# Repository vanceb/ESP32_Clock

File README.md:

# ESP32_Clock
Clock based on the ESP32

A follow-on from the NightClock

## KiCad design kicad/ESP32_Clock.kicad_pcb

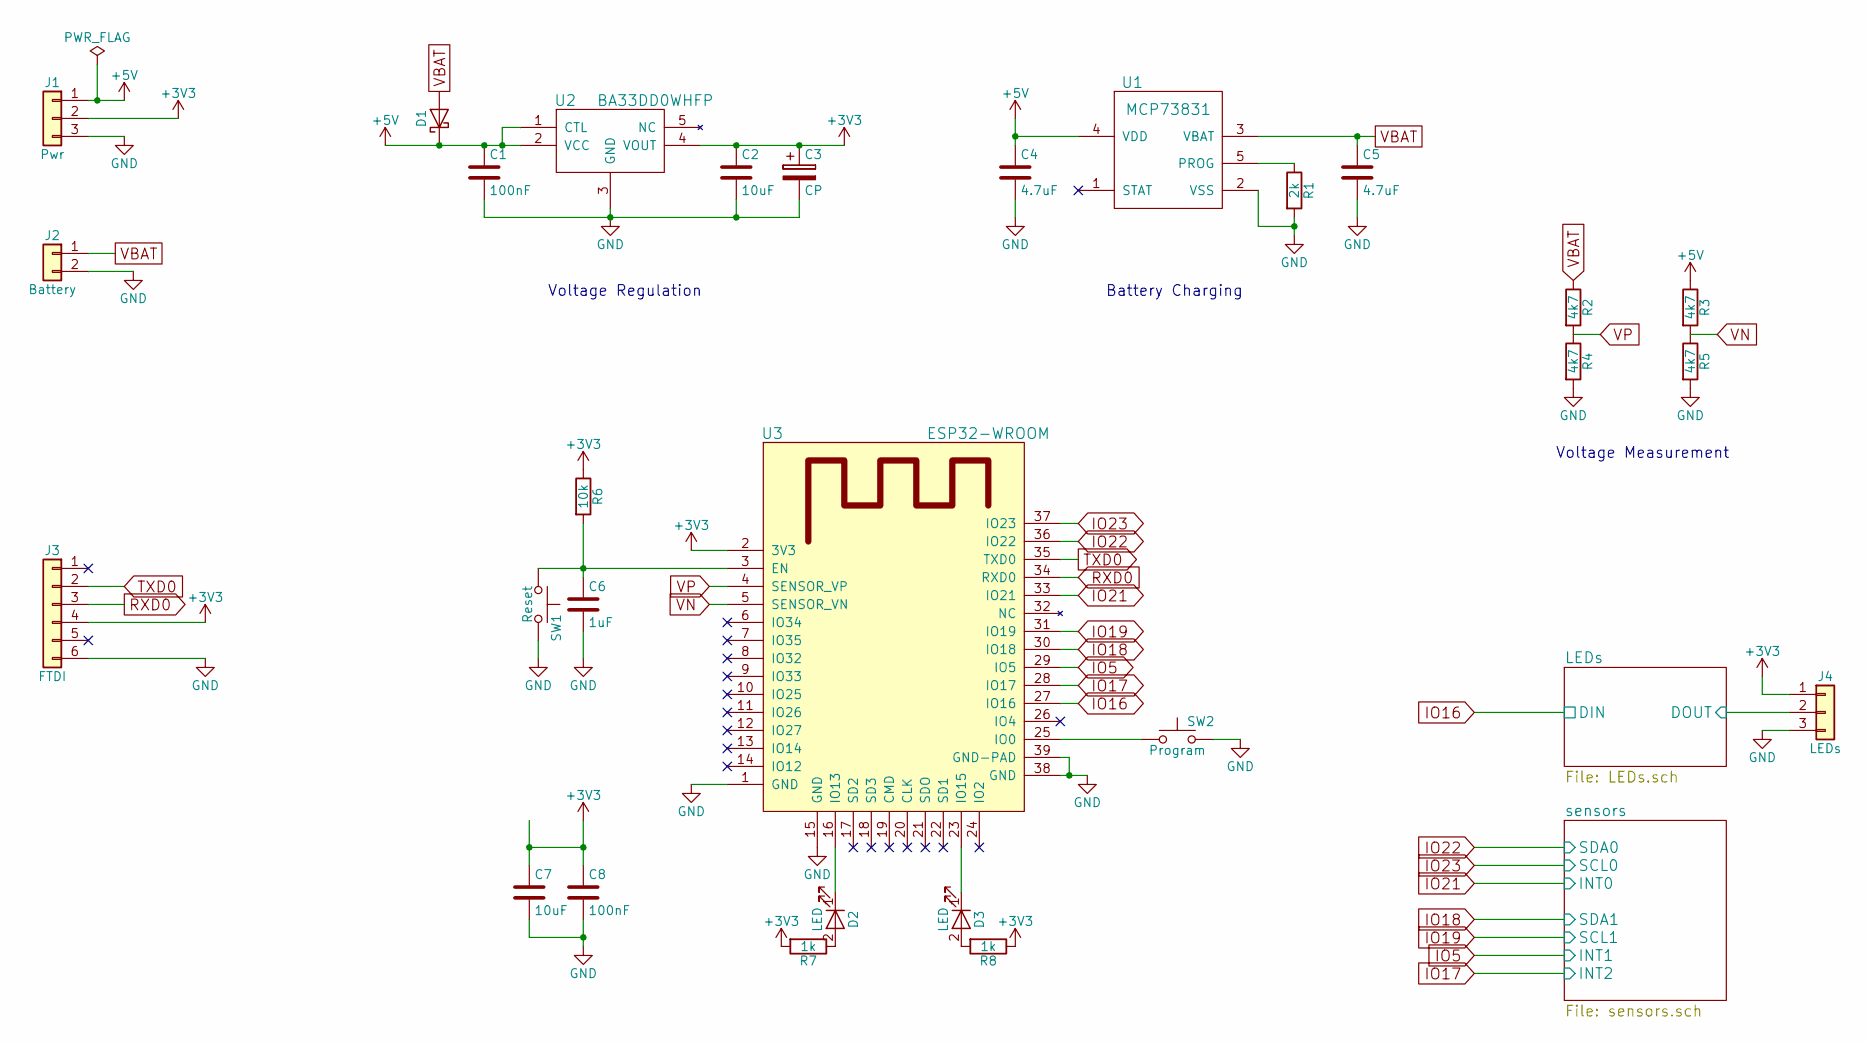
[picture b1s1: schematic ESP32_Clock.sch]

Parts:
C1, C8: 100nF; C_0603_HandSoldering
C2, C7: 10uF; C_0805_HandSoldering
C3: CP; CP_Radial_D8.0mm_P3.50mm
C4, C5: 4.7uF; C_0805_HandSoldering
C6: 1uF; C_0805_HandSoldering
D1: D_SMA_Handsoldering
D2, D3: LED; LED_0603_HandSoldering
J1: Pwr; Pin_Header_Straight_1x03_Pitch2.54mm
J2: Battery; JST_PH_S2B-PH-K_02x2.00mm_Angled
J3: FTDI; Pin_Header_Straight_1x06_Pitch2.54mm
J4: LEDs; Pin_Header_Straight_1x03_Pitch2.54mm
R1: 2k; R_0603_HandSoldering
R2, R3, R4, R5: 4k7; R_0603_HandSoldering
R6: 10k; R_0603_HandSoldering
R7, R8: 1k; R_0603_HandSoldering
SW1: Reset; SW_SPST_EVPBF
SW2: Program; SW_SPST_EVPBF
U1: MCP73831; SOT-23-5_HandSoldering
U2: BA33DD0WHFP; LDO
U3: ESP32-WROOM

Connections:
+3V3: C2.1, C3.1, C7.1, C8.1, J1.2, J3.4, J4.1, R6.1, R7.2, R8.1, U2.4 (VOUT), U3.2 (3V3); also elsewhere on the board
+5V: C1.1, C4.1, D1.1 (K), J1.1, R3.1, U1.4 (VDD), U2.1 (CTL), U2.2 (VCC)
/LEDs/DOUT: J4.2; also elsewhere on the board
GND: C1.2, C2.2, C3.2, C4.2, C5.2, C6.2, C7.2, C8.2, J1.3, J2.2, J3.6, J4.3, R1.2, R4.2, R5.2, SW1.2, SW2.2, U1.2 (VSS), U2.3 (GND), U3.1 (GND), U3.15 (GND), U3.38 (GND), U3.39 (GND-PAD); also elsewhere on the board
IO5: U3.29 (IO5); also elsewhere on the board
IO16: U3.27 (IO16); also elsewhere on the board
IO17: U3.28 (IO17); also elsewhere on the board
IO18: U3.30 (IO18); also elsewhere on the board
IO19: U3.31 (IO19); also elsewhere on the board
IO21: U3.33 (IO21); also elsewhere on the board
IO22: U3.36 (IO22); also elsewhere on the board
IO23: U3.37 (IO23); also elsewhere on the board
unnamed: C6.1, R6.2, SW1.1, U3.3 (EN)
unnamed: D2.1 (K), U3.16 (IO13)
unnamed: D2.2 (A), R7.1
unnamed: D3.1 (K), U3.23 (IO15)
unnamed: D3.2 (A), R8.2
unnamed: R1.1, U1.5 (PROG)
unnamed 24: SW2.1, U3.25 (IO0); also elsewhere on the board
RXD0: J3.3, U3.34 (RXD0)
TXD0: J3.2, U3.35 (TXD0)
VBAT: C5.1, D1.2 (A), J2.1, R2.1, U1.3 (VBAT)
VN: R3.2, R5.1, U3.5 (SENSOR_VN)
VP: R2.2, R4.1, U3.4 (SENSOR_VP)

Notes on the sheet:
Voltage Regulation
Battery Charging
Voltage Measurement

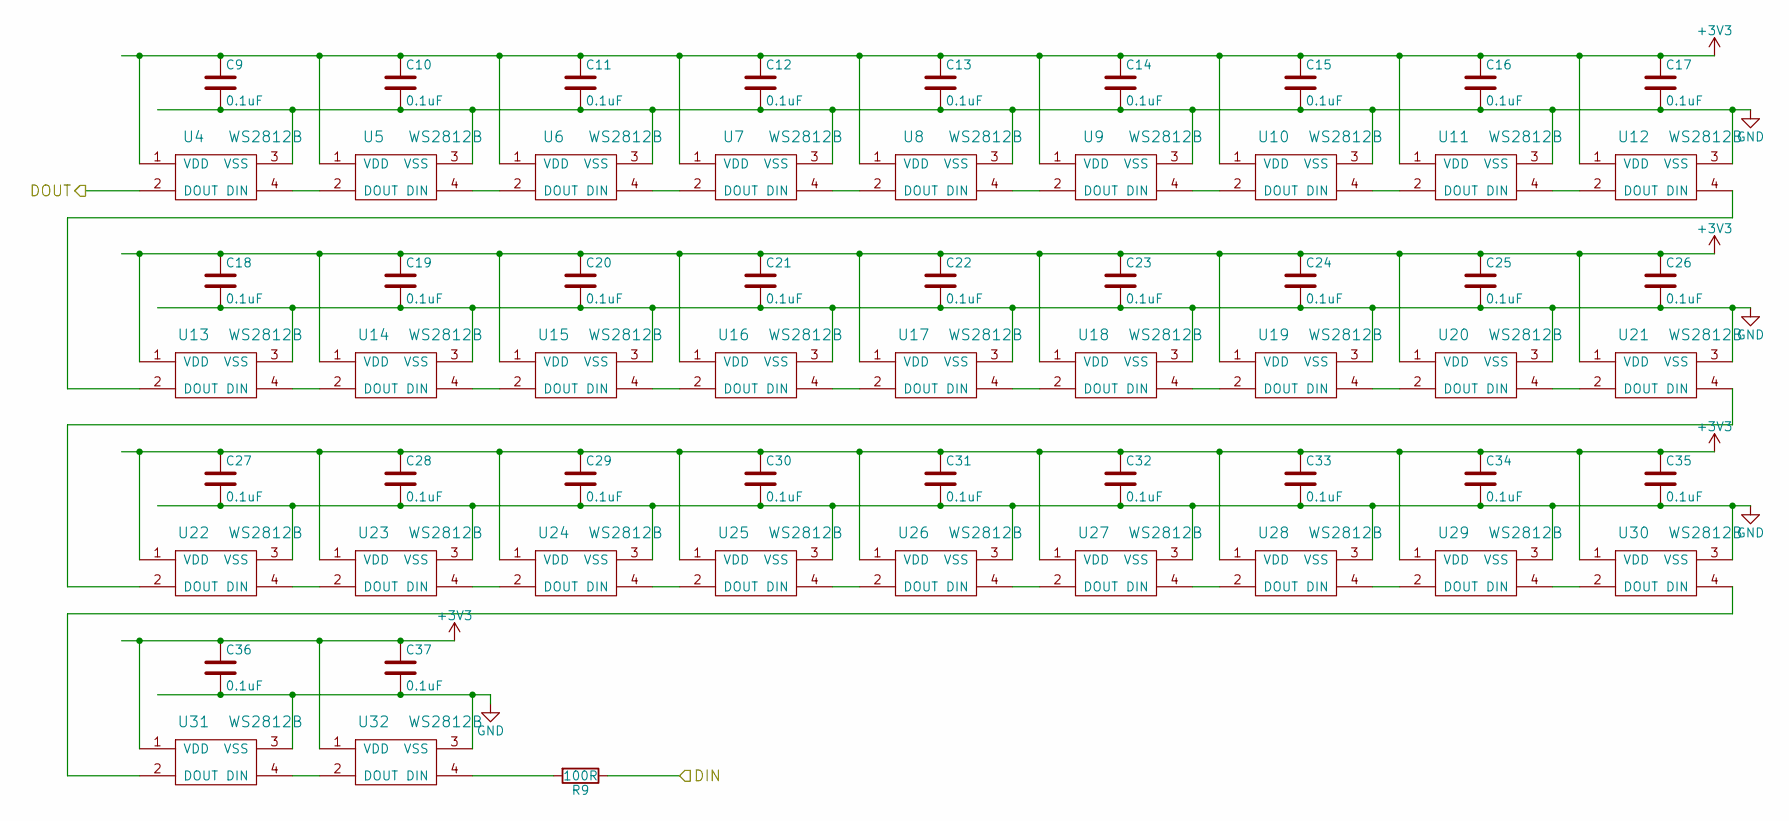
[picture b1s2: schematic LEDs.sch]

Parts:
C9, C10, C11, C12, C13, C14, C15, C16, C17, C18, C19, C20, C21, C22, C23, C24, C25, C26, C27, C28, C29, C30, C31, C32, C33, C34, C35, C36, C37: 0.1uF; C_0603_HandSoldering
R9: 100R; R_0603_HandSoldering
U4, U5, U6, U7, U8, U9, U10, U11, U12, U13, U14, U15, U16, U17, U18, U19, U20, U21, U22, U23, U24, U25, U26, U27, U28, U29, U30, U31, U32: WS2812B; LED_WS2812B-PLCC4

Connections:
+3V3: C9.1, C10.1, C11.1, C12.1, C13.1, C14.1, C15.1, C16.1, C17.1, C18.1, C19.1, C20.1, C21.1, C22.1, C23.1, C24.1, C25.1, C26.1, C27.1, C28.1, C29.1, C30.1, C31.1, C32.1, C33.1, C34.1, C35.1, C36.1, C37.1, U4.1 (VDD), U5.1 (VDD), U6.1 (VDD), U7.1 (VDD), U8.1 (VDD), U9.1 (VDD), U10.1 (VDD), U11.1 (VDD), U12.1 (VDD), U13.1 (VDD), U14.1 (VDD), U15.1 (VDD), U16.1 (VDD), U17.1 (VDD), U18.1 (VDD), U19.1 (VDD), U20.1 (VDD), U21.1 (VDD), U22.1 (VDD), U23.1 (VDD), U24.1 (VDD), U25.1 (VDD), U26.1 (VDD), U27.1 (VDD), U28.1 (VDD), U29.1 (VDD), U30.1 (VDD), U31.1 (VDD), U32.1 (VDD); also elsewhere on the board
/LEDs/DOUT: U4.2 (DOUT); also elsewhere on the board
GND: C9.2, C10.2, C11.2, C12.2, C13.2, C14.2, C15.2, C16.2, C17.2, C18.2, C19.2, C20.2, C21.2, C22.2, C23.2, C24.2, C25.2, C26.2, C27.2, C28.2, C29.2, C30.2, C31.2, C32.2, C33.2, C34.2, C35.2, C36.2, C37.2, U4.3 (VSS), U5.3 (VSS), U6.3 (VSS), U7.3 (VSS), U8.3 (VSS), U9.3 (VSS), U10.3 (VSS), U11.3 (VSS), U12.3 (VSS), U13.3 (VSS), U14.3 (VSS), U15.3 (VSS), U16.3 (VSS), U17.3 (VSS), U18.3 (VSS), U19.3 (VSS), U20.3 (VSS), U21.3 (VSS), U22.3 (VSS), U23.3 (VSS), U24.3 (VSS), U25.3 (VSS), U26.3 (VSS), U27.3 (VSS), U28.3 (VSS), U29.3 (VSS), U30.3 (VSS), U31.3 (VSS), U32.3 (VSS); also elsewhere on the board
IO16: R9.1; also elsewhere on the board
unnamed: R9.2, U32.4 (DIN)
unnamed: U4.4 (DIN), U5.2 (DOUT)
unnamed: U5.4 (DIN), U6.2 (DOUT)
unnamed: U6.4 (DIN), U7.2 (DOUT)
unnamed: U7.4 (DIN), U8.2 (DOUT)
unnamed: U8.4 (DIN), U9.2 (DOUT)
unnamed: U9.4 (DIN), U10.2 (DOUT)
unnamed: U10.4 (DIN), U11.2 (DOUT)
unnamed: U11.4 (DIN), U12.2 (DOUT)
unnamed: U12.4 (DIN), U13.2 (DOUT)
unnamed: U13.4 (DIN), U14.2 (DOUT)
unnamed: U14.4 (DIN), U15.2 (DOUT)
unnamed: U15.4 (DIN), U16.2 (DOUT)
unnamed: U16.4 (DIN), U17.2 (DOUT)
unnamed: U17.4 (DIN), U18.2 (DOUT)
unnamed: U18.4 (DIN), U19.2 (DOUT)
unnamed: U19.4 (DIN), U20.2 (DOUT)
unnamed: U20.4 (DIN), U21.2 (DOUT)
unnamed: U21.4 (DIN), U22.2 (DOUT)
unnamed: U22.4 (DIN), U23.2 (DOUT)
unnamed: U23.4 (DIN), U24.2 (DOUT)
unnamed: U24.4 (DIN), U25.2 (DOUT)
unnamed: U25.4 (DIN), U26.2 (DOUT)
unnamed: U26.4 (DIN), U27.2 (DOUT)
unnamed: U27.4 (DIN), U28.2 (DOUT)
unnamed: U28.4 (DIN), U29.2 (DOUT)
unnamed: U29.4 (DIN), U30.2 (DOUT)
unnamed: U30.4 (DIN), U31.2 (DOUT)
unnamed: U31.4 (DIN), U32.2 (DOUT)

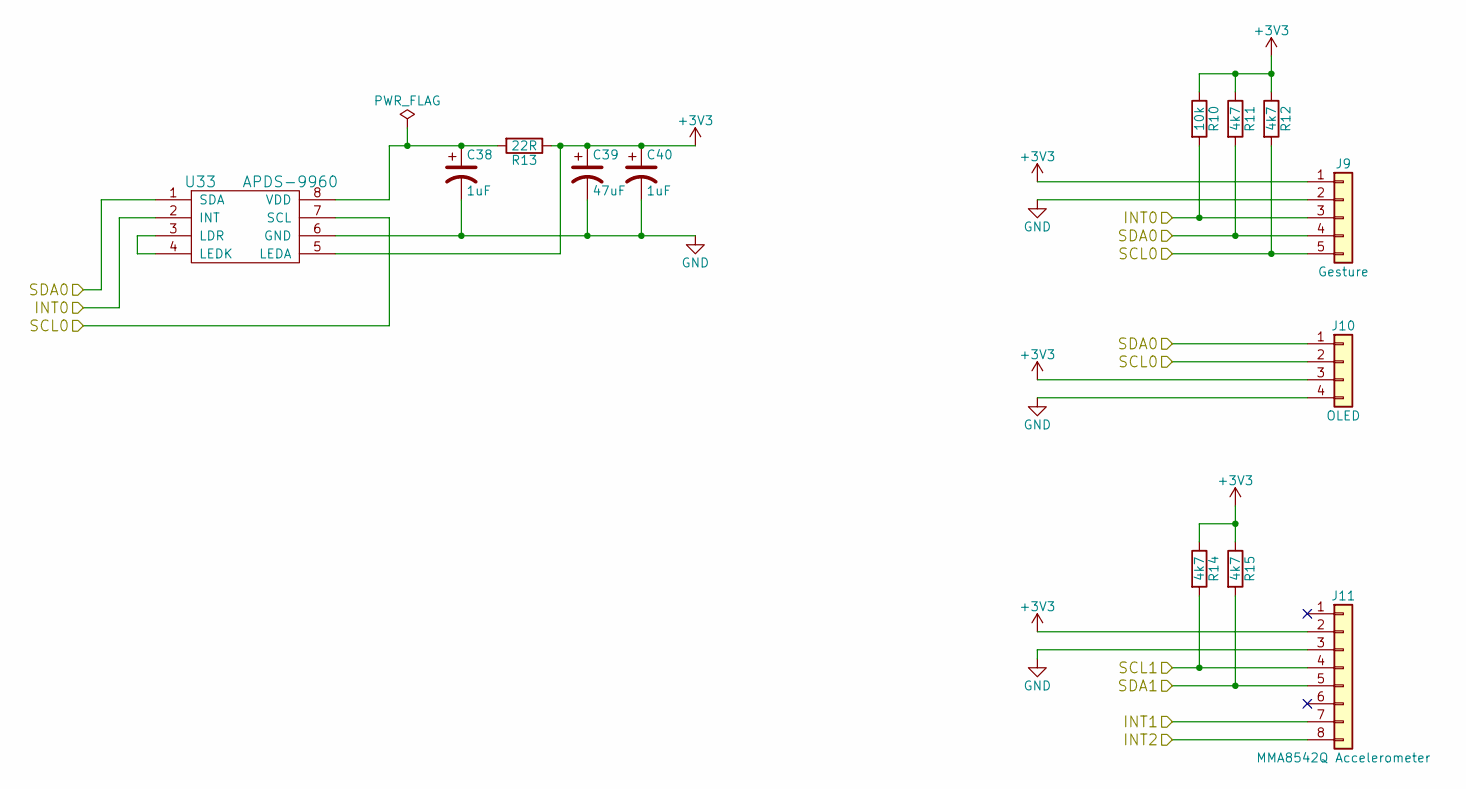
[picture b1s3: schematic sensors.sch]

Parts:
C38, C40: 1uF; CP_Tantalum_Case-R_EIA-2012-12_Hand
C39: 47uF; CP_Tantalum_Case-A_EIA-3216-18_Hand
J9: Gesture; Pin_Header_Straight_1x05_Pitch2.54mm
J10: OLED; 128x32_OLED
J11: MMA8542Q Accelerometer; Pin_Header_Straight_1x08_Pitch2.54mm
R10: 10k; R_0603_HandSoldering
R11, R12, R14, R15: 4k7; R_0603_HandSoldering
R13: 22R; R_0603_HandSoldering
U33: APDS-9960; ADPS-9960

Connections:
+3V3: C39.1, C40.1, J9.1, J10.3, J11.2, R10.1, R11.1, R12.1, R13.1, R14.1, R15.1, U33.5 (LEDA); also elsewhere on the board
GND: C38.2, C39.2, C40.2, J9.2, J10.4, J11.3, U33.6 (GND); also elsewhere on the board
IO5: J11.7; also elsewhere on the board
IO17: J11.8; also elsewhere on the board
IO18: J11.5, R15.2; also elsewhere on the board
IO19: J11.4, R14.2; also elsewhere on the board
IO21: J9.3, R10.2, U33.2 (INT); also elsewhere on the board
IO22: J9.4, J10.1, R11.2, U33.1 (SDA); also elsewhere on the board
IO23: J9.5, J10.2, R12.2, U33.7 (SCL); also elsewhere on the board
unnamed: C38.1, R13.2, U33.8 (VDD)
unnamed: U33.3 (LDR), U33.4 (LEDK)

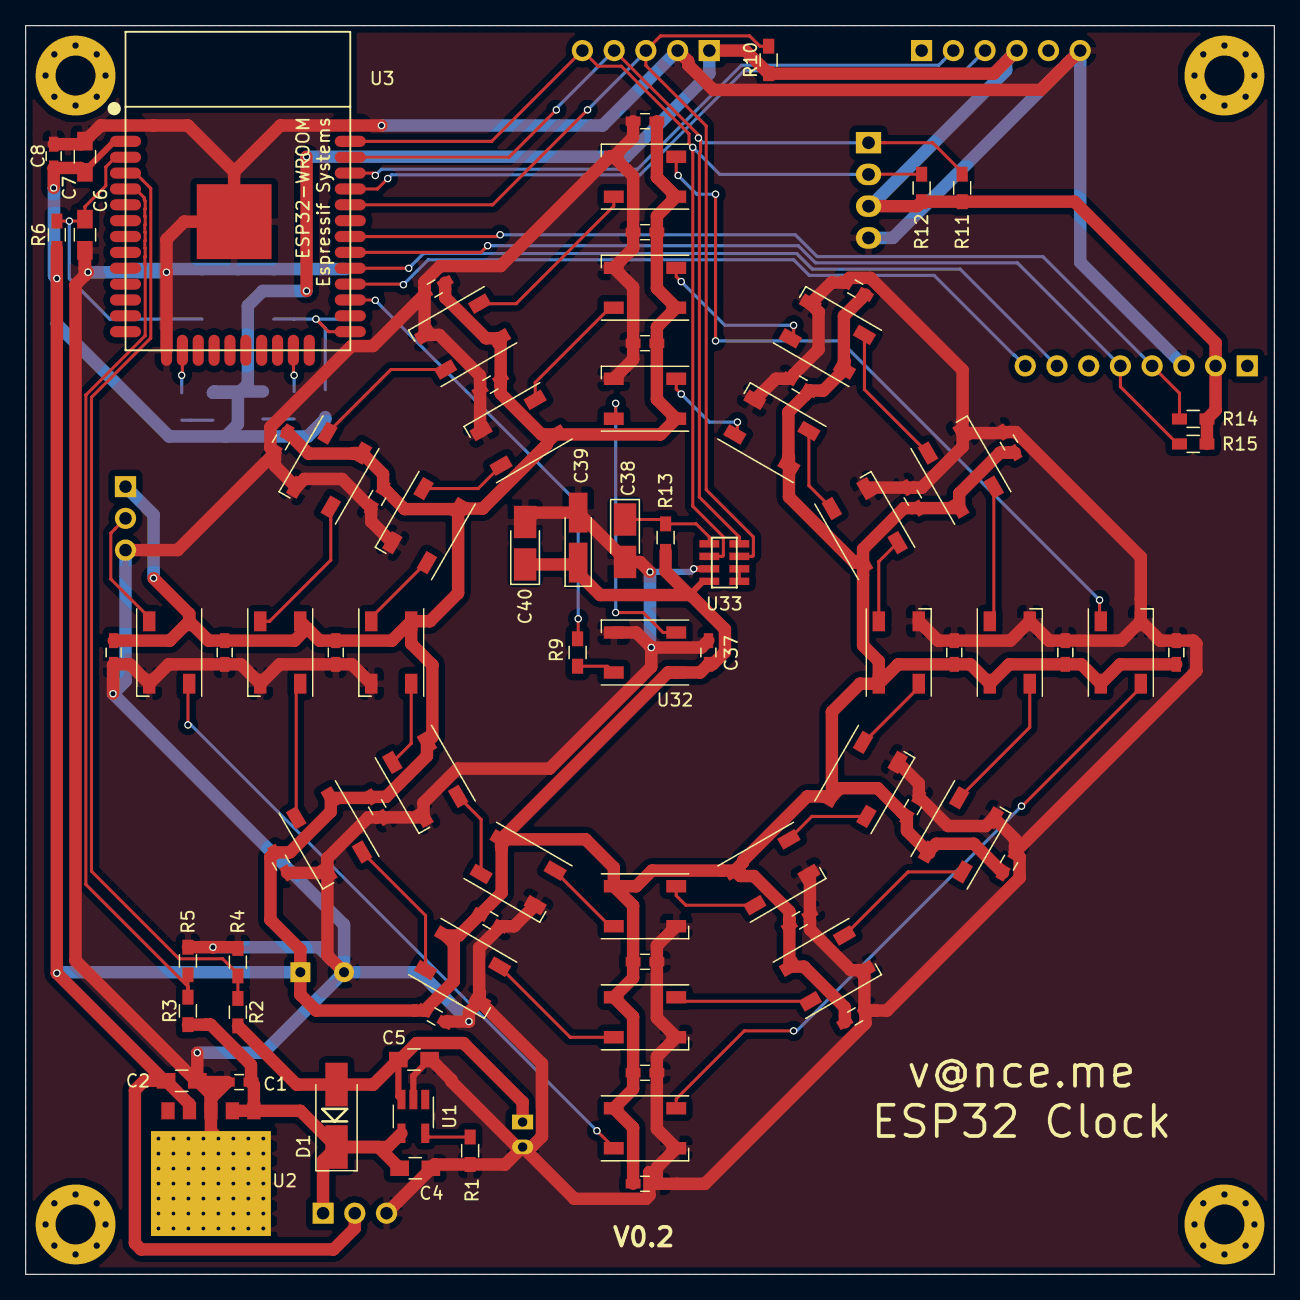
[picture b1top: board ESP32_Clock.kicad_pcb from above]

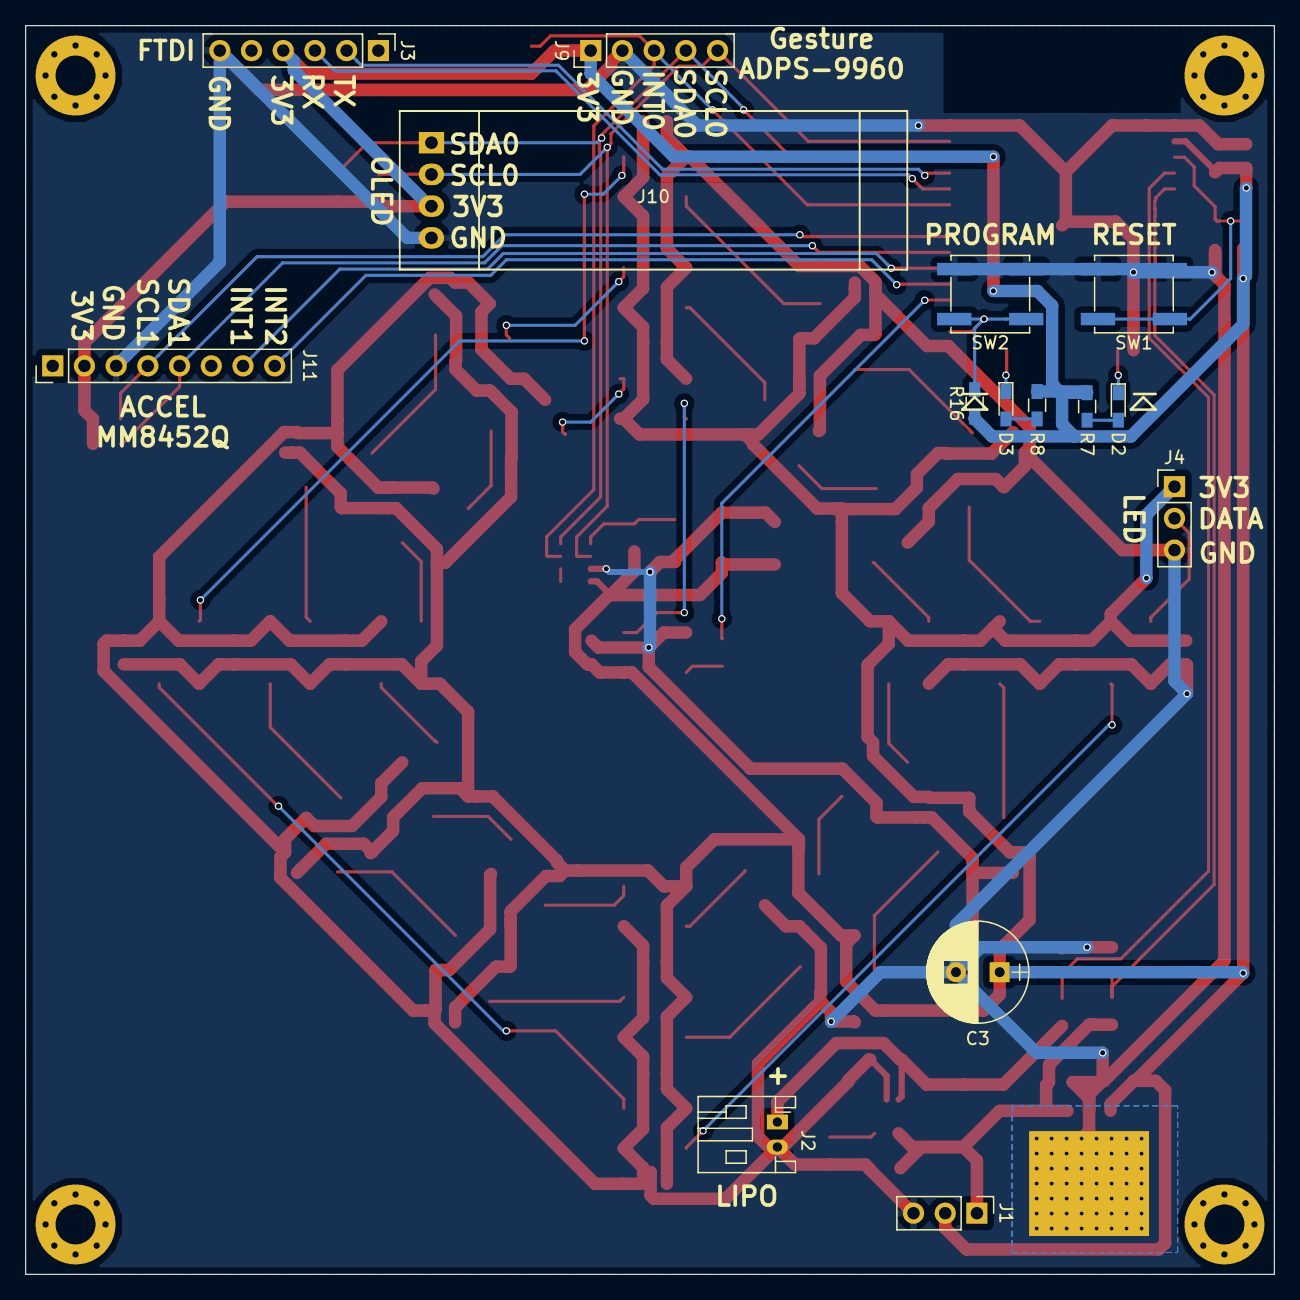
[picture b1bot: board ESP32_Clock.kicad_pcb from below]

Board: 2 copper layers, 100.0 x 100.0 mm, 101 parts (15 on the bottom side), 55 nets.

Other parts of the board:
R16: 10k; R_0603_HandSoldering

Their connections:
+3V3: R16.1; also elsewhere on the board
unnamed 24: R16.2; also elsewhere on the board

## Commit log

2018-02-28 Initial kicad commit
2018-02-28 Platformio project initiation
2018-03-30 Board design almost ready for fabrication
2018-04-09 PCB at v0.1, and some simple modifications to AWS IOT code using the esp-idf framework
2018-04-09 excluded the build folder
2018-05-29 Initial changes after first board test
2018-05-29 staging changes
2018-06-20 Updated hardware design and removed test idf-code
2018-06-20 added starting block code based on the aws_iot example code
2018-06-21 First combined example of display and mqtt - still only examples
2018-06-21 Now communicating on sensible mqtt topics which include the ID (Mac address) of the ESP
2018-06-23 Added pullup to IO0 to be safe during boot
2018-07-19 Version 0.2 of the board layout - submitted for manufacture
2018-07-22 First working key-value parser
2018-07-25 added .gitignore and tidied up keyvalue.c
2018-07-30 Solder paste template cutting
2018-07-30 Clock display showing the time
2018-07-31 Fading clock display added
2018-07-31 Documented and tidies code
2018-09-09 Updated to kicad 5
2018-09-09 wip ota update
2018-09-19 Turned on 'Signed App Verification' to add security to OTA images
2018-09-19 Successful OTA upgrade
2018-09-23 Moved from aws_iot to mqtts. Not yet tested queued transmit
2018-09-24 Now working sending messages via mqtt
2018-09-24 Added correct subscribe task
2018-11-07 Updated telemetry to fixed size messages and implemented some basic actions for commands
2018-11-07 Intermediate commit - still occasionally crashes whilst ssl encrypt/decrypt
2018-11-07 Now doesn't crash randomly on mqtt receive
2018-11-07 Removed small memory leak and re-enabled mqtt echo of incoming commands
2018-11-20 Changed the key-value processing
2018-11-22 Completed refactor of telemetry and key-value processing
2018-11-22 Added wifi status on startup and during clock display
2018-11-22 Added brightness control to display
2018-11-23 Added serialization to string for key value pairs
2018-11-28 Basic working version with integrated wifi_manager
2018-11-28 Connection status indications added through colour of markers on the clock
2018-11-28 Allowed ESP_ERR_WIFI_TIMEOUT as a result of a wifi scan without reboot
2018-11-29 Tidied OTA code
2018-11-30 Tidied the telemetry code
2018-12-02 Updated project name in Makefile
2018-12-18 Brightness working, gesture detection OK without screen, but too many replections from screen to work properly
2018-12-18 BOM produced
2019-03-22 Fixed clock overrun issue which stopped status updates after just over an hour
2019-03-26 Tweaked brightness of the cardinal point markers
